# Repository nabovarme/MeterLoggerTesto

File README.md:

MeterLogger
===========

Get data via IR and log it to iOS device via SoftModem FSK.
https://code.google.com/p/arms22/source/browse/#svn%2Ftrunk%2FSoftModem

Testo protocol
--------------
IR Printer emulator for Testo flue gas analysator <http://www.testousa.com/combustion/testo-310-residential-combustion-analyzer.html>.

Coded for pic18f2550 compiled with SDCC

send data at 19200 bps over serial

protocol http://members.ziggo.nl/kees.van.der.sanden/downloads/82240bte.pdf (HP-IR, HP48)

http://www.keesvandersanden.nl/calculators/hp82240.php

Video showing "printing": https://www.youtube.com/watch?v=RM3XE1EymNQ

Kamstrup Meter Protocol
-----------------------
http://www.kamstrup.com/media/2105/IEC61107_comprotocol.pdf

300 baud, 1 start bit, 7 data bits, even parity and 1 stop bit

To meter:
/?![CR][LF]

http://kamstrup.com/media/19757/file.pdf

The protocol is based on half duplex serial asynchronous communication with the setup: 8 databits, no parity and 2 stopbits. The data bit rate is 1200 or 2400 baud. CRC16 is used in both request and response.

http://ing.dk/blog/tal-med-din-elmaaler-og-ingenioeren-120524
"300 bps, 7 databit, lige paritet"
"/ ? ! CR NL"

https://github.com/bsdphk/PyDLMS/blob/master/dlms.py

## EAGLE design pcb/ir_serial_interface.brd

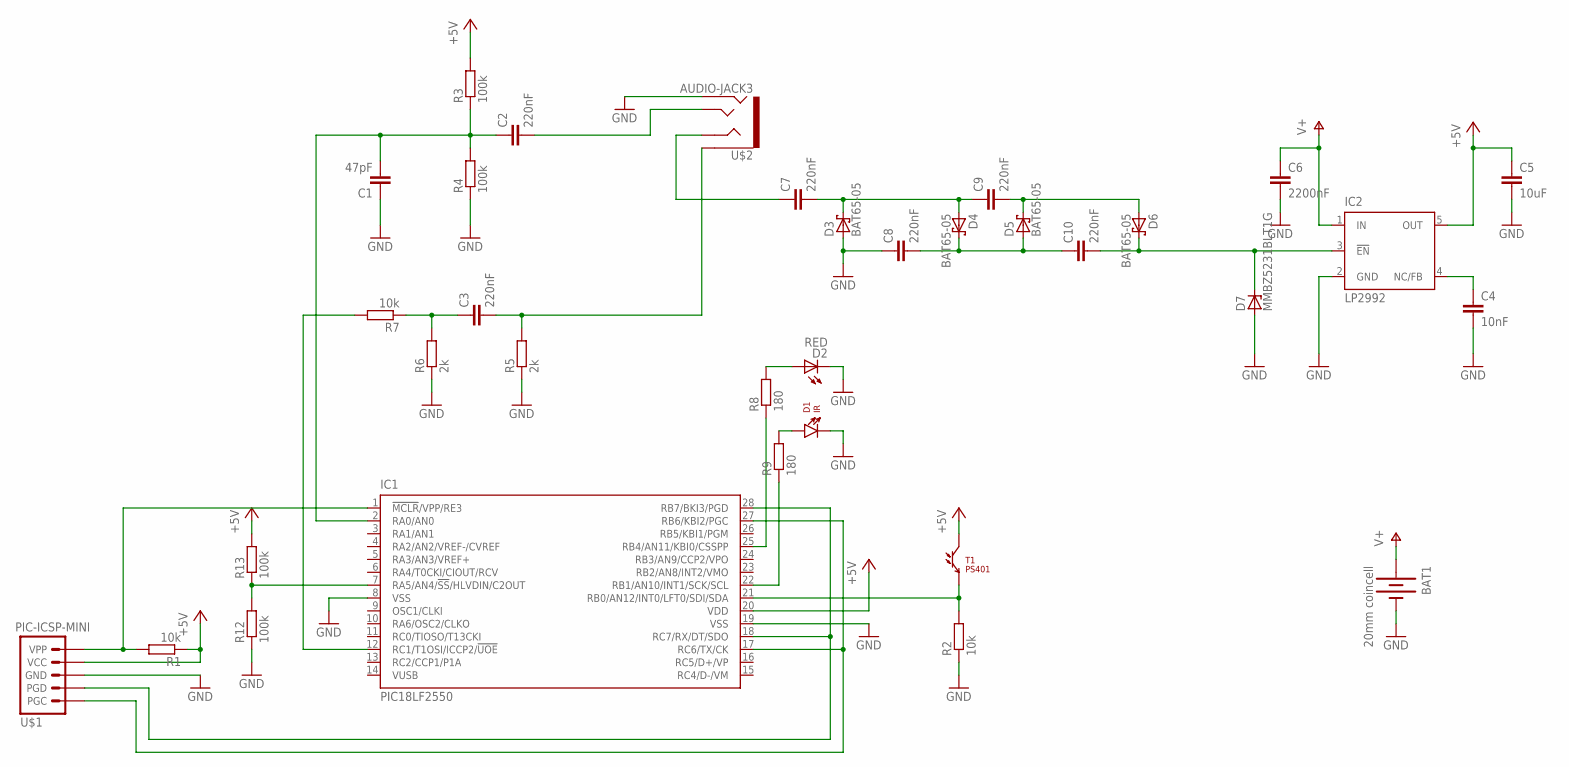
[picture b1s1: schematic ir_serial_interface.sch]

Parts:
BAT1: 20mm coincell; BATTCOM_20MM_PTH
C1: 47pF; 0805
C2, C3: 220nF; 0805
C4: 10nF; C0805
C5: 10uF; C0805
C6: 2200nF; C0805
C7, C8, C9, C10: 220nF; C0805
D1: IR; LTE-302
D2: RED; LED-1206
D3, D4, D5, D6: BAT65-05; SOT23
D7: MMBZ5231BLT1G; SOT23
IC1: PIC18LF2550; SO28W
IC2: LP2992; SOT23-DBV
R1, R2, R7: 10k; M0805
R3, R4, R12, R13: 100k; M0805
R5, R6: 2k; M0805
R8, R9: 180; M0805
T1: PS401; LTR-301
U$1: PIC-ICSP-MINI
U$2: AUDIO-JACK3; AUDIO-JACK-TRRS-SMD

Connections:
+5V: C5.1, IC1.20 (VDD), IC2.5 (OUT), R1.1, R3.2, R13.2, T1.C, U$1.2 (VCC)
GND: BAT1.2 (-), C1.1, C4.2, C5.2, C6.2, C8.1, D1.C, D2.C, D3.1 (A), D7.1 (A), IC1.8 (VSS), IC1.19 (VSS), IC2.2 (GND), R2.1, R4.1, R5.1, R6.1, R12.1, U$1.3 (GND), U$2.RING2
unnamed: IC1.21 (RB0/AN12/INT0/LFT0/SDI/SDA), R2.2, T1.E
unnamed: IC1.1 (!MCLR!/VPP/RE3), R1.2, U$1.1 (VPP)
unnamed: IC1.18 (RC7/RX/DT/SDO), IC1.28 (RB7/BKI3/PGD), U$1.4 (PGD)
unnamed: IC1.17 (RC6/TX/CK), IC1.27 (RB6/KBI2/PGC), U$1.5 (PGC)
unnamed: C2.2, U$2.TIP
unnamed: C1.2, C2.1, IC1.2 (RA0/AN0), R3.1, R4.2
unnamed: C3.2, R5.2, U$2.EARTH
unnamed: C3.1, R6.2, R7.1
unnamed: IC1.12 (RC1/T1OSI/ICCP2/!UOE), R7.2
unnamed: D2.A, R8.2
unnamed: IC1.25 (RB4/AN11/KBI0/CSSPP), R8.1
unnamed: C7.1, U$2.RING1
unnamed: C7.2, C9.1, D3.3 (C), D4.1 (A)
unnamed: D1.A, R9.2
unnamed: IC1.22 (RB1/AN10/INT1/SCK/SCL), R9.1
unnamed: IC1.7 (RA5/AN4/!SS!/HLVDIN/C2OUT), R12.2, R13.1
unnamed: C9.2, D5.3 (C), D6.1 (A)
unnamed: C8.2, C10.1, D4.3 (C), D5.1 (A)
unnamed: C10.2, D6.3 (C), D7.3 (C), IC2.3 (!EN)
unnamed: C4.1, IC2.4 (NC/FB)
V+: BAT1.1 (+), C6.1, IC2.1 (IN)

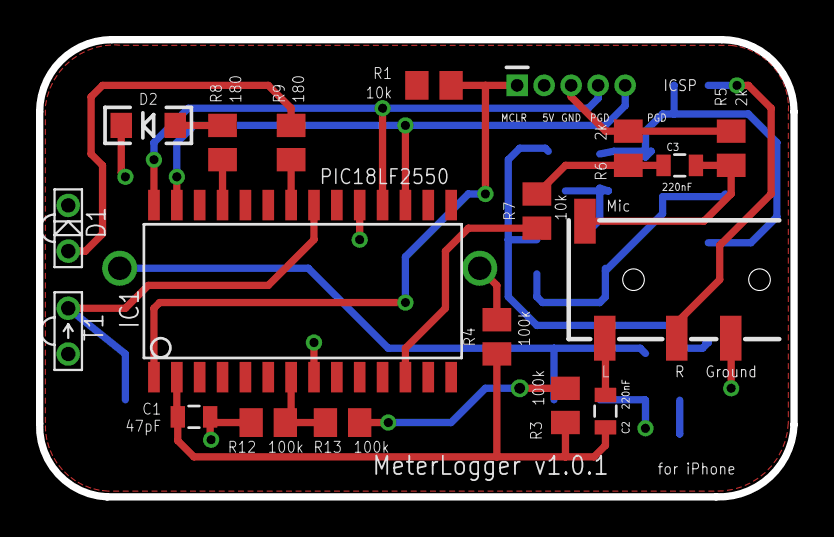
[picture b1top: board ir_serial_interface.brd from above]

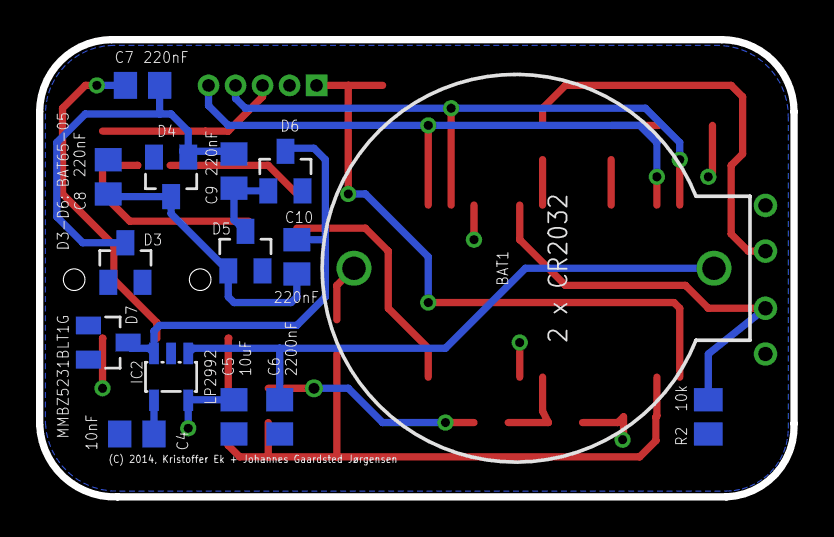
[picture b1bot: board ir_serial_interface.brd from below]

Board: 2 copper layers, 41.9 x 25.4 mm, 34 parts (15 on the bottom side), 23 nets.

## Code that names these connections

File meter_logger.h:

#define DEBUG_BUFFER_MAX (128)

#define BYTETOBINARYPATTERN "%d%d%d%d%d%d%d%d"
#define BYTETOBINARY(byte)  \
	(byte & 0x80 ? 1 : 0), \
	(byte & 0x40 ? 1 : 0), \
	(byte & 0x20 ? 1 : 0), \
	(byte & 0x10 ? 1 : 0), \
	(byte & 0x08 ? 1 : 0), \
	(byte & 0x04 ? 1 : 0), \
	(byte & 0x02 ? 1 : 0), \
	(byte & 0x01 ? 1 : 0)

#define sleep() __asm sleep __endasm

#define TIMER0_TESTO			0xF323	// ~ 4 * 427us @ 8MHz
#define TIMER0_RS232_300		0xe61b	// ~ 3.3ms @ 8 MHz
#define TIMER0_RS232_1200		0xf9ae
#define TIMER0_FSK				0xF99F	// @ 8MHz

#define TIMER1_RELOAD 0xF853    // 1 ms @ 8MHz
#define TIMER2_RELOAD	0x00	// ~ 5 ms @ 8Mhz
#define TIMER3_RELOAD	0x0000	// ~ 131 ms @ 4MHz

#define SOFT_MODEM_BAUD_RATE	(1225)
#define SOFT_MODEM_LOW_FREQ		(4900)
#define SOFT_MODEM_HIGH_FREQ	(7350)
		
#define FSK_TX_SLEEP			(4)
#define RS232_TX_SLEEP			(12)

#define OUTPUT_STATE (0)
#define INPUT_STATE (1)

#define TRIS_COMP1		TRISAbits.RA0
#define TRIS_COMP2		TRISAbits.RA1
#define COMP1_PIN		PORTAbits.RA0
#define COMP2_PIN		PORTAbits.RA1

#define TRIS_V_SENSE	TRISAbits.RA5

#define TRIS_IR_PIN		TRISBbits.RB0
#define IR_PIN			PORTBbits.RB0

#define TRIS_LED_PIN	TRISBbits.RB4
#define LED_PIN			PORTBbits.RB4

#define TRIS_IR_LED_PIN	TRISBbits.RB1 
#define IR_LED_PIN		PORTBbits.RB1

#define TRIS_DEBUG_PIN	TRISBbits.RB2
#define DEBUG_PIN		PORTBbits.RB2

#define TRIS_DEBUG2_PIN	TRISBbits.RB3
#define DEBUG2_PIN		PORTBbits.RB3

#define TRIS_DEBUG3_PIN	TRISBbits.RB4
#define DEBUG3_PIN		PORTBbits.RB4

#define TRIS_PWM_PIN	TRISCbits.RC1
#define PWM_PIN			PORTCbits.RC1

#define TRIS_RX_PIN		TRISCbits.RC7
#define RX_PIN			PORTCbits.RC7

#define TRIS_TX_PIN		TRISCbits.RC6
#define TX_PIN			PORTCbits.RC6

#define TICK 855
#define TICK_ADJ 200

#define PROTO_TESTO_DEMO		(255)
#define PROTO_TESTO				(254)
#define PROTO_KAMSTRUP			(253)
#define PROTO_IEC61107			(252)
#define PROTO_BATTERY_LEVEL		(251)

void sleep_ms(unsigned int ms);

void init_system();

unsigned int get_dev_id();

void my_usart_open();

unsigned char reverse(unsigned char b);

unsigned char testo_valid_err_corr(unsigned int c);

void testo_ir_enable();
void testo_ir_disable();

void rs232_8n2_tx_enable(unsigned int t);
void rs232_8n2_tx_disable();

void rs232_8n2_rx_enable(unsigned int t);
void rs232_8n2_rx_disable();
void rs232_8n2_tx_byte(unsigned char c);

void rs232_7e1_tx_enable(unsigned int t);
void rs232_7e1_tx_disable();

void rs232_7e1_rx_enable(unsigned int t);
void rs232_7e1_rx_disable();
void rs232_7e1_tx_byte(unsigned char c);

void fsk_tx_enable();
void fsk_tx_disable();

void fsk_rx_enable();
void fsk_rx_disable();

void send_fsk_high(void);
void send_fsk_low(void);
void fsk_tx_byte(unsigned char c);

unsigned int fifo_in_use();
unsigned char fifo_put(unsigned char c);
unsigned char fifo_get(unsigned char  *c);
unsigned char fifo_snoop(unsigned char *c, unsigned int pos);

unsigned int get_battery_level();

void flash_led(unsigned char ms);

void _debug();
void _debug2();

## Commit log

2014-03-28 Start
2014-03-29 should work
2014-03-30 working
2014-03-30 detects start bit
2014-03-30 swich instead of if else
2014-03-30 can detect data
2014-03-30 better debug
2014-03-30 bi-phase detection code, but looses some frames
2014-03-30 regression - no bi-phase code, but no lost frames
2014-03-30 all frames received + bi-phase code
2014-03-30 working bi-phase decoding
2014-03-30 cleanup
2014-03-30 data processed by bi-phase decoder and returned bytewise via serial port 8n1 @ 9600 bps
2014-03-30 error-fix
2014-03-30 more debugging - serial data out should work now but untested
2014-03-30 info stuff
2014-03-31 more debug
2014-03-31 decoding almost work
2014-04-01 almost working
2014-04-01 tmr0 values measured with real incoming data
2014-04-01 8 first bytes ok
2014-04-01 wrong placement for ir_proto.data_len++
2014-04-01 simplification
2014-04-01 naming timer_0_ms -> timer_1_ms
2014-04-01 modified - git test
2014-04-01 more files
2014-04-01 only print data with valid error correction bits
2014-04-03 interrup on rising edge with phototransistor
2014-04-06 pretty printing
2014-04-06 debug
2014-04-06 rising edge -> falling edge
2014-04-06 first 8 bytes are received correctly
2014-04-10 phototransistor should work according to logic analyzer
2014-04-10 working - there must be an error in error correction code
2014-04-10 clean up
2014-04-10 working error correction
2014-04-11 enter sleep mode when last bit is received and wake on int0 (ir input)
2014-04-11 missing comment
2014-04-11 added link to video
2014-04-11 not working version
2014-04-12 working on pic18f2550 and in simulator (gpsim)
2014-04-12 testing...
2014-04-12 patched error that coused timer to reset when it should receive first start bits
2014-04-12 without debug out
2014-04-12 working pwm output at 22kHz
2014-04-13 testing manchester encoding
2014-04-13 pic18f2550 in readme
2014-04-14 added pre-support for multiple protocols on ir
2014-04-16 more preparations for soft uart
2014-04-16 more cleanup
2014-04-16 working soft uart tx test byte 250
2014-04-16 working at 2400bps 8n1
2014-04-16 fifo
2014-04-16 kamstrup tx is working @ 2400 bps 8n1 no framing error + reading from fifo
2014-04-17 pwm test signal
2014-04-23 configuring analog comparator and voltage ref
2014-04-24 analog comparator at 0v + debug ouput
2014-04-24 comparator at 2,65625 V
2014-04-24 disable function
2014-04-24 rename hijack to fsk
2014-04-25 detects start bit of fsk
2014-04-26 no sleep_ms()
2014-04-26 mostly working fsk demodulator/decoder
2014-04-26 first byte working not second
2014-04-27 typo == -> =
2014-04-27 working fsk decoder - outputs on serial port
2014-04-27 use fifo for data handling
2014-04-27 8MHz - not working
2014-04-27 fsk tx star bit timer
2014-04-27 right frequency 7350Hz
2014-04-27 test fsk tx signal
2014-04-27 example of output from testo 310
2014-04-29 1024 byte fifo working - tested with testo_ir_enable
2014-04-29 working pulses high and low
2014-04-29 working fsk tx
2014-04-29 fsk tx data test
2014-04-29 overflow in fifo index counter - fixed
2014-04-29 var cleanup
2014-04-30 when cmd = 0 on fsk_rx it listens for data from testo in 40 seconds and return it on serial
2014-04-30 send received data via fsk
2014-04-30 cmd = 255: echo test
2014-04-30 obanksel=2 smaller code size
2014-04-30 more time to send data to echo test
2014-04-30 better receiving with new correct filter
2014-04-30 no debug
2014-04-30 output on fsk - ready to test with iOS
2014-04-30 pic18f2550
2014-04-30 more doc
2014-04-30 project rename
2014-04-30 MSB fsk tx
2014-04-30 working fsk tx minimum time: 4 ms
2014-04-30 merged to master
2014-04-30 LSB -> MSB
2014-05-01 more rename + DEBUG + OUTPUT_ON_SERIAL
2014-05-01 right input polarity from minijack
2014-05-01 less code
2014-05-01 blink led when receiving from testo
2014-05-01 testo: returns data via fsk/serial when break for more than 50 ms
2014-05-01 testo: returns data via fsk/serial when break for more than 50 -> 100
2014-05-02 echo test: returns data when iOS stopped sending data
2014-05-02 more doc about kamstrup
2014-05-02 more doc Kamstrup Meter Protocol
2014-05-02 DEBUG_LED_ON_FSK_*
2014-05-05 timing changes
2014-05-08 some protocol sniffing
2014-05-08 more info and data
2014-05-08 serial speed
2014-05-09 real data
2014-05-23 more info
2014-05-23 typo
2014-05-24 result decoding info
2014-05-27 start of kmp test
2014-05-28 working ir data from kamstrup multical 601
2014-05-28 kmpGetSerialNo
2014-05-29 kmpSetClock
2014-05-29 kmpGetRegister
2014-05-30 Mac OS X program to test KMP class
2014-05-30 missing files
2014-05-30 start of byte stuff methods
2014-05-30 decodeFrame
    start
2014-05-30 decodeFrame
2014-05-30 prepare for kmpUnstuff
2014-05-30 GetSerialNo working
2014-05-31 saves in responseData dictionary
2014-05-31 getRegister + kmpByteStuff
2014-05-31 decoding getRegister responseData
2014-05-31 serial port init at 1200bps 8n2
2014-05-31 ui cleanup
    text input field is register
2014-05-31 moved to nabovarme/kmp_demo
2014-06-04 preparing for kamstrup
2014-06-05 kamstrup kmp protocol
2014-06-06 rs232
2014-06-06 RS232_TX working
2014-06-06 rs232 ir inverted output
2014-06-07 rs232 rx bit framing done
2014-06-07 rs232 rx software modem works
2014-06-07 kamstrup kmp working
2014-06-07 wait for kamstrup device to stop sending data
    instead of fixed value of 1 second, when waiting for kmp reply
2014-06-07 debug + RS232_TX: only run timer 0 when needed
2014-06-07 rs232_tx_byte() enter timer interrupt handler now
2014-06-08 hmm.. .must be a timing bug here...
    check it with Logic analyzer
2014-06-08 timing issues done
2014-06-08 wait for fsk data double time
2014-06-08 BUG: not enough proc cycles when doing fsk_tx_byte
    and sleeping simultaniously. sleep_ms(4) takes 60-70 mS
2014-06-08 debug interrupt usage on DEBUG2_PIN
2014-06-08 no isr debug
2014-06-08 DEBUG enables serial debug
2014-06-09 PCB: R channel enables MeterLogger
2014-06-09 added
2014-06-10 PROTO_* values changed to avoid 0
2014-06-10 no pin debug + no fsk idling + main() protocol timing
2014-06-10 bug solved
2014-06-10 kamstrup mode: return \r when no data
    + sleep after fsk_tx_enable to let the fsk init start
2014-06-11 sleep longer after fsk tx
2014-06-11 faster sleep_ms() and no overrun
2014-06-12 multical iii doc
2014-06-12 multical iii docs + pcb
2014-06-12 OUTPUT_ON_SERIAL working and sends via fsk
    DEBUG gives state description
2014-06-13 battery check, command 252
2014-06-13 PCB: board layout done
2014-06-14 PCB: routing done
2014-06-14 better space layout
2014-06-14 silk screen cleanup
2014-06-14 PCB: missing routes
2014-06-14 cut round - wider outline path
2014-06-14 silk screen on name layer not value layer
    + component values
2014-06-14 PCB: silk complete
2014-06-14 PCB: boad too short
2014-06-14 PCB: Martens rettelser
2014-06-14 PCB: missing zener
2014-06-15 PCB: Martens rettelser, layout done.
2014-06-15 PCB: mirrored text
2014-06-15 PCB: moved text
2014-06-15 PCB: moved text away from edge
2014-06-15 PCB: final adjustments
2014-06-15 PCB: text on right layer
2014-06-15 PCB: final touch
2014-06-15 space around connectors and opto
2014-06-17 faster fsk and rs232 tx
    no sleep after *_tx_enable()
    *_tx_byte() wait for byte to complete sending
    tx_enable(unsigned int t) takes speed parameter (timer0 value)
2014-06-17 use device id to decide adc resolution
2014-06-17 added rs232_7e1_*
    missing implementation in interrupt handlers, copied from rs232_8n1
2014-06-17 RS232_7E1_TX
    done for test
2014-06-17 rs232_7e1_tx works now
2014-06-18 rename kamstrup multical to iec 61107
2014-06-18 multical -> IEC61107
2014-06-18 IEC61107/IEC62056-21
2014-06-18 Kamstrup IEC 61107 doc
    for kamstrup 382
2014-06-18 rs232_7e1_rx working
2014-06-18 no DEBUG_RS232_*_RX
2014-06-18 truncate data to 7 bit
2014-06-18 missing check for parity bit/ 2. stop bit
    logic must be false
2014-06-19 fixed rx timer int logic for databits/parity/stop
2014-06-20 debugging
2014-06-20 formatted debug messages
2014-06-20 less debug
2014-06-20 dont return 7e1 if parity error
2014-06-20 DEBUG: transmit it anyway, multical iii sends last byte with parity error
    DEBUG: transmit it anyway, multical iii sends last byte with parity
    error
2014-06-21 empty queue after each protocol request
2014-06-21 sleep_ms() overflow bug?
    changed to alternative, but slower implementation
2014-06-21 gpl header added
2014-06-22 casting not needed
2014-06-23 only declare volatile if necessary
2014-06-30 PCB: fix
    comparator was connected to battery/2 instead ov 5V/2
    version 1.0.1
2014-07-02 PCB: no zener
2014-07-03 PCB: reuse programmer header for serial debug
2014-07-03 PCB: with zener and serial on ICSP
2014-07-03 spice simulation of voltage multiplier
2014-07-07 PCB: visible programmer pin header values
2014-07-09 led blink at boot
2014-07-10 FSK TX/RX LED debug
2015-09-29 multical iii perl test

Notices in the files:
pcb/ir_serial_interface.brd:
(C) 2014, Kristoffer Ek + Johannes Gaardsted Jørgensen
parts and their libraries:
SparkFun-Connectors: Licensing: CC v3.0 Share-Alike You are welcome to use this library for commercial purposes.
SparkFun-Sensors: Licensing: Creative Commons ShareAlike 4.0 International - https://creativecommons.org/licenses/by-sa/4.0
